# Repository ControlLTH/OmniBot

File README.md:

# OmniBot
Documentation for OmniBots

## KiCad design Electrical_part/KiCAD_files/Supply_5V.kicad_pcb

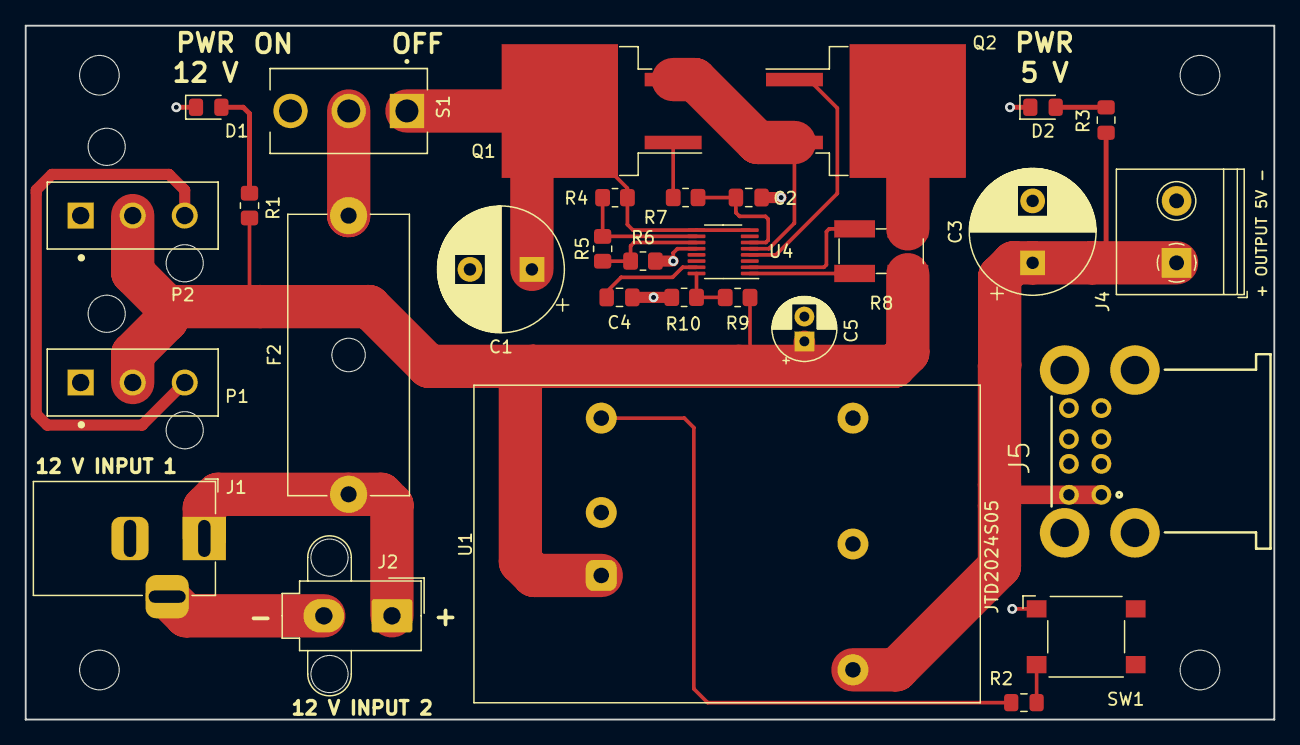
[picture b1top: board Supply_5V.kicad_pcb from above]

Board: 2 copper layers, 100.8 x 56.0 mm, 34 parts (0 on the bottom side), 23 nets.

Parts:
C1, C3: EEEFK1A222AQ; CP_Radial_D10.0mm_P5.00mm
C2, C4: C; C_0805_2012Metric_Pad1.18x1.45mm_HandSolder
C5: C_Polarized; CP_Radial_D5.0mm_P2.00mm
D1, D2: LED; LED_0805_2012Metric_Pad1.15x1.40mm_HandSolder
F2: Fuse; Fuseholder_Cylinder-5x20mm_Schurter_0031_8201_Horizontal_Op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
H1, H2, H3, H4: MountingHole; MountingHole_3.2mm_M3
J1: 12 V INPUT; BarrelJack_Horizontal
J2: Conn_01x02_Male; Molex_Mini-Fit_Jr_5566-02A2_2x01_P4.20mm_Vertical
J4: Screw_Terminal_01x02; TerminalBlock_Philmore_TB132_1x02_P5.00mm_Horizontal
J5: USB1035-XX-X-X-X-B_REVE; GCT_USB1035-XX-X-X-X-B_REVE
P1, P2: 39-30-1039; MOLEX_39-30-1039
Q1: FDB33N25; TO-263-2
Q2: FDB3682; TO-263-2
R1, R4, R5, R6, R7, R9, R10: R; R_0805_2012Metric_Pad1.20x1.40mm_HandSolder
R2, R3: R; R_0805_2012Metric_Pad1.15x1.40mm_HandSolder
R8: R_Shunt; R_Shunt_Ohmite_LVK25
S1: OFF ON; SW_100SP1T1B4M2QE
SW1: SW_Push_Dual; SW_SPST_Omron_B3FS-100xP
U1: JTD2024S05; Converter_DCDC_XP_POWER_JTDxxxxxxx_THT
U4: LTC4364IMS; MSOP-16_3x4.039mm_P0.5mm

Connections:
GND: C1.2, C2.1, C3.2, C4.1, C5.2, D1.1 (K), D2.1 (K), J1.2, J4.2, J5.4A (GND1), J5.4B (GND2), P1.1, P2.1, R6.1, R10.1, SW1.1, U1.2 (-VIN), U1.5 (-VOUT), U4.12 (GND)
unnamed: C1.1, Q1.2 (D), R4.2, S1.1, U4.8 (VCC), U4.9 (~SHDN)
unnamed: C2.2, R7.1, U4.6 (HGATE)
unnamed: C3.1, J4.1, J5.1A (VBUS1), J5.1B (VBUS2), R3.2, U1.3 (+VOUT)
unnamed: C4.2, U4.15 (TMR)
unnamed: C5.1, P1.2, P2.2, R1.2, R8.4, R9.2, U1.1 (+VIN)
unnamed: D1.2 (A), R1.1
unnamed: D2.2 (A), R3.1
unnamed: F2.1, J1.1, J2.1
unnamed: F2.2, S1.2
unnamed: J1.3, J2.2
unnamed: P1.3, P2.3
unnamed: Q1.1 (G), R7.2
unnamed: Q1.3 (S), Q2.3 (S), U4.5 (SOURCE)
unnamed: Q2.1 (G), U4.4 (DGATE)
unnamed: Q2.2 (D), R8.1
unnamed: R2.1, U1.6 (On/~Off)
unnamed: R2.2, SW1.3
unnamed: R4.1, R5.2, U4.10 (UV)
unnamed: R5.1, R6.2, U4.11 (OV)
unnamed: R8.2, U4.1 (OUT)
unnamed: R8.3, U4.2 (SENSE)
unnamed: R9.1, R10.2, U4.16 (FB)

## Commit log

2022-06-02 Subfolders created
2022-06-03 added files
2022-06-04 added values
